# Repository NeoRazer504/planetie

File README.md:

This is a project inspired by [Starbie](https://github.com/SharKingStudios/Starbie/tree/main). It's called Planetie since its sort of a rip off and more planet based rather than a star. It was made it KiCad for hackclub's Half Life program
What it does is it displays the main sprite on a OLED screen doing things depending on input from the user or the environment using buttons, and motion and environment sensors.
Key differences from the main Starbie project include that the PCB has a different shape:

And it also had firmware changes to add a galactic alphabet trail and use my own custom made sprite:

To assemble it, get the circuit board printed, get the parts from the BOM, and solder it accordingly. To get the firmware on Xiao, plug it into your computer, hold the reset button, and drag the firmware file into the folder for the Xiao on your computer.

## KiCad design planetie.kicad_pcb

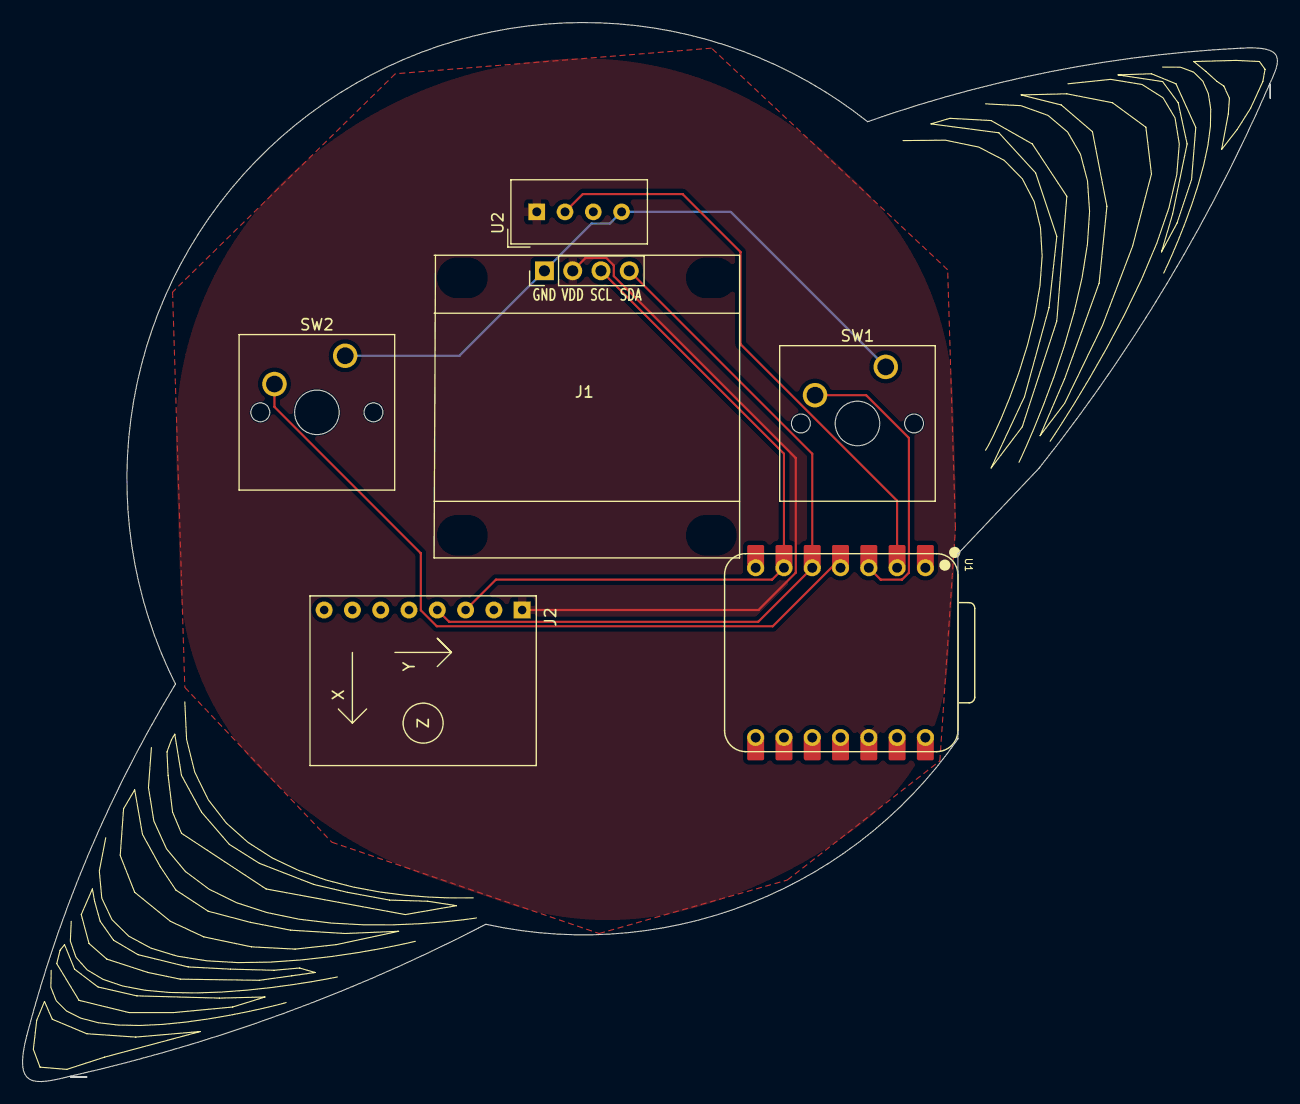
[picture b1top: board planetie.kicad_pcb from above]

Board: 2 copper layers, 112.7 x 95.1 mm, 6 parts (0 on the bottom side), 7 nets.

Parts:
J1: Conn_01x04_Pin; Display_128x64_096_I2C
J2: Conn_01x08_Pin; MPU6050_Module
SW1, SW2: SW_Push; SW_Cherry_MX_1.00u_PCB
U1: XIAO-ESP32-C3-SMD; XIAO-ESP32C3-DIP
U2: DHT11; Aosong_DHT11_5.5x12.0_P2.54mm

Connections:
+3.3V: J1.2, J2.1, U1.12 (3V3), U2.1 (VDD)
/SCL: J1.3, J2.3, U1.6 (GPIO7_D5_SCL)
/SDA: J1.4, J2.4, U1.5 (GPIO6_D4_SDA)
GND: J1.1, J2.2, SW1.1, SW2.1, U1.13 (GND), U2.4 (GND)
unnamed: U1.2 (GPIO3_A1_D1), U2.2 (DATA)
unnamed: SW1.2, U1.3 (GPIO4_A2_D2)
unnamed: SW2.2, U1.4 (GPIO5_A3_D3)

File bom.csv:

Designator,Footprint,Quantity,Value,LCSC Part #
J1,Display_128x64_096_I2C,1,Conn_01x04_Pin,
J2,MPU6050_Module,1,Conn_01x08_Pin,
"SW1, SW2",SW_Cherry_MX_1.00u_PCB,2,SW_Push,
U1,XIAO-ESP32C3-DIP,1,XIAO-ESP32-C3-SMD,
U2,Aosong_DHT11_5.5x12.0_P2.54mm,1,DHT11,
